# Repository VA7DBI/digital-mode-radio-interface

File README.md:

A basic project to provide an isolated audio and CAT control interface.   Connectes to the host PC via USB and provides a Serial Port providing a CAT Control interface and an Audio CODEC.

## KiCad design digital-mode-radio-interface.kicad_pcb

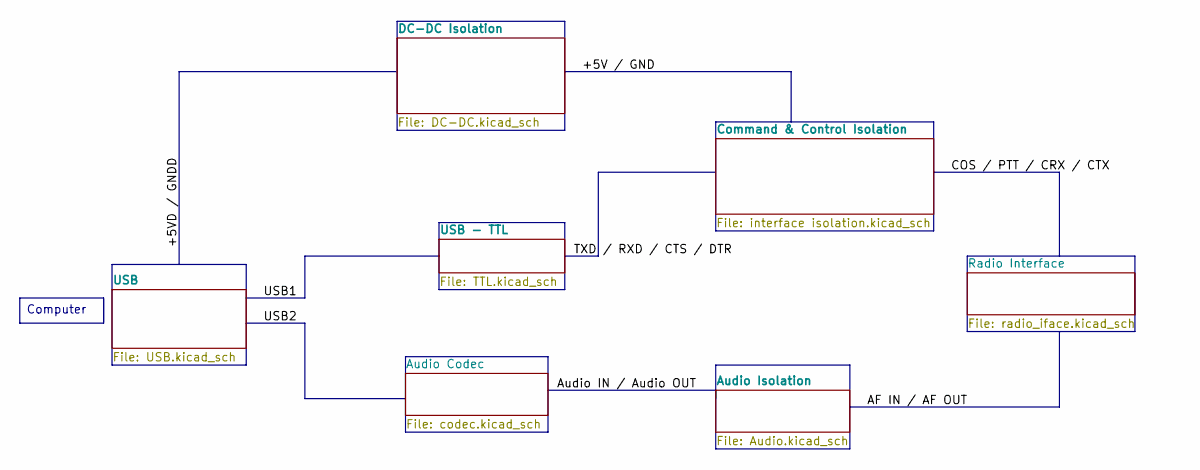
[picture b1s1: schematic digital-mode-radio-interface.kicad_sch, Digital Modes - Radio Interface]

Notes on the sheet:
Computer

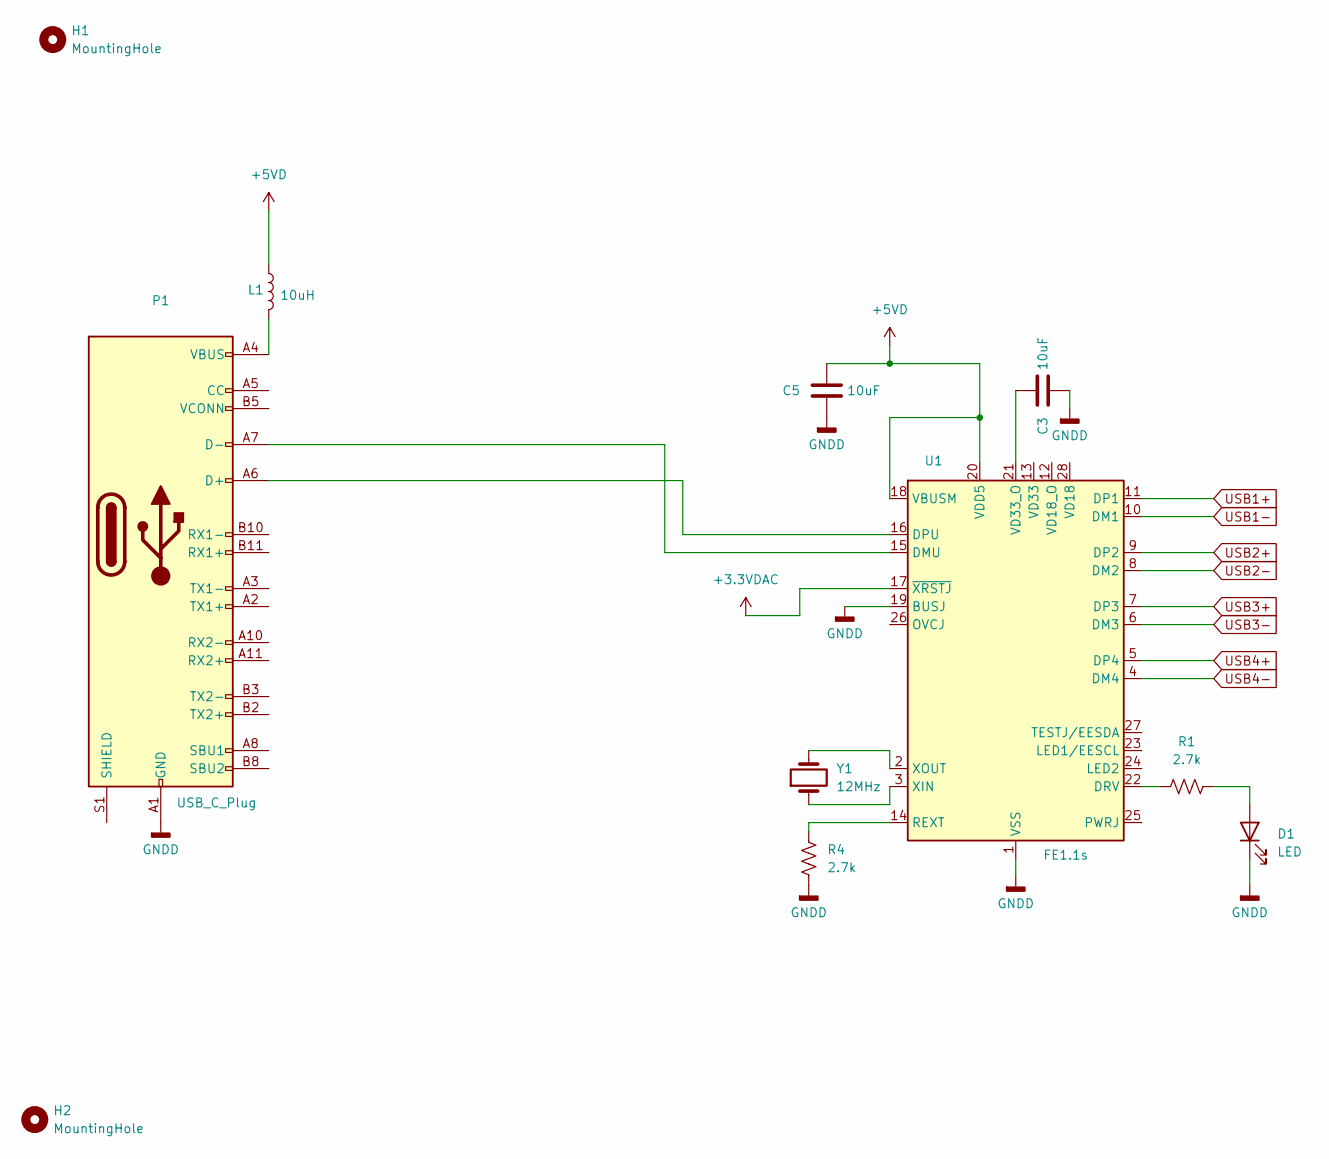
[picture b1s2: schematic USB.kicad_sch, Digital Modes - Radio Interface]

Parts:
C3, C5: 10uF; C_0201_0603Metric
D1: LED; LED_0201_0603Metric
H1, H2: MountingHole; MountingHole_3.2mm_M3
L1: 10uH; L_CommonModeChoke_Coilcraft_0805USB
P1: USB_C_Plug; USB_C_Receptacle_GCT_USB4085
R1, R4: 2.7k; R_0201_0603Metric
U1: FE1.1s; SSOP-28_3.9x9.9mm_P0.635mm
Y1: 12MHz; Crystal_SMD_FOX_FE-2Pin_7.5x5.0mm_HandSoldering

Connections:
+3.3VDAC: U1.17 (~XRSTJ); also elsewhere on the board
+5VD: C5.1, L1.1, U1.18 (VBUSM), U1.20 (VDD5); also elsewhere on the board
GNDD: C3.2, C5.2, D1.1 (K), P1.A1 (GND), P1.A12 (GND), P1.B1 (GND), P1.B12 (GND), R4.2, U1.1 (VSS), U1.19 (BUSJ); also elsewhere on the board
unnamed: D1.2 (A), R1.2
unnamed: L1.2, P1.A4 (VBUS), P1.A9 (VBUS), P1.B4 (VBUS), P1.B9 (VBUS)
unnamed: P1.A6 (D+), U1.16 (DPU)
unnamed: P1.A7 (D-), U1.15 (DMU)
unnamed: R1.1, U1.22 (DRV)
unnamed: R4.1, U1.14 (REXT)
unnamed: C3.1, U1.21 (VD33_O)
unnamed: U1.3 (XIN), Y1.1
unnamed: U1.2 (XOUT), Y1.2
USB1+: U1.11 (DP1); also elsewhere on the board
USB1-: U1.10 (DM1); also elsewhere on the board
USB2+: U1.9 (DP2)
USB2-: U1.8 (DM2)
USB3+: U1.7 (DP3)
USB3-: U1.6 (DM3)
USB4+: U1.5 (DP4)
USB4-: U1.4 (DM4)

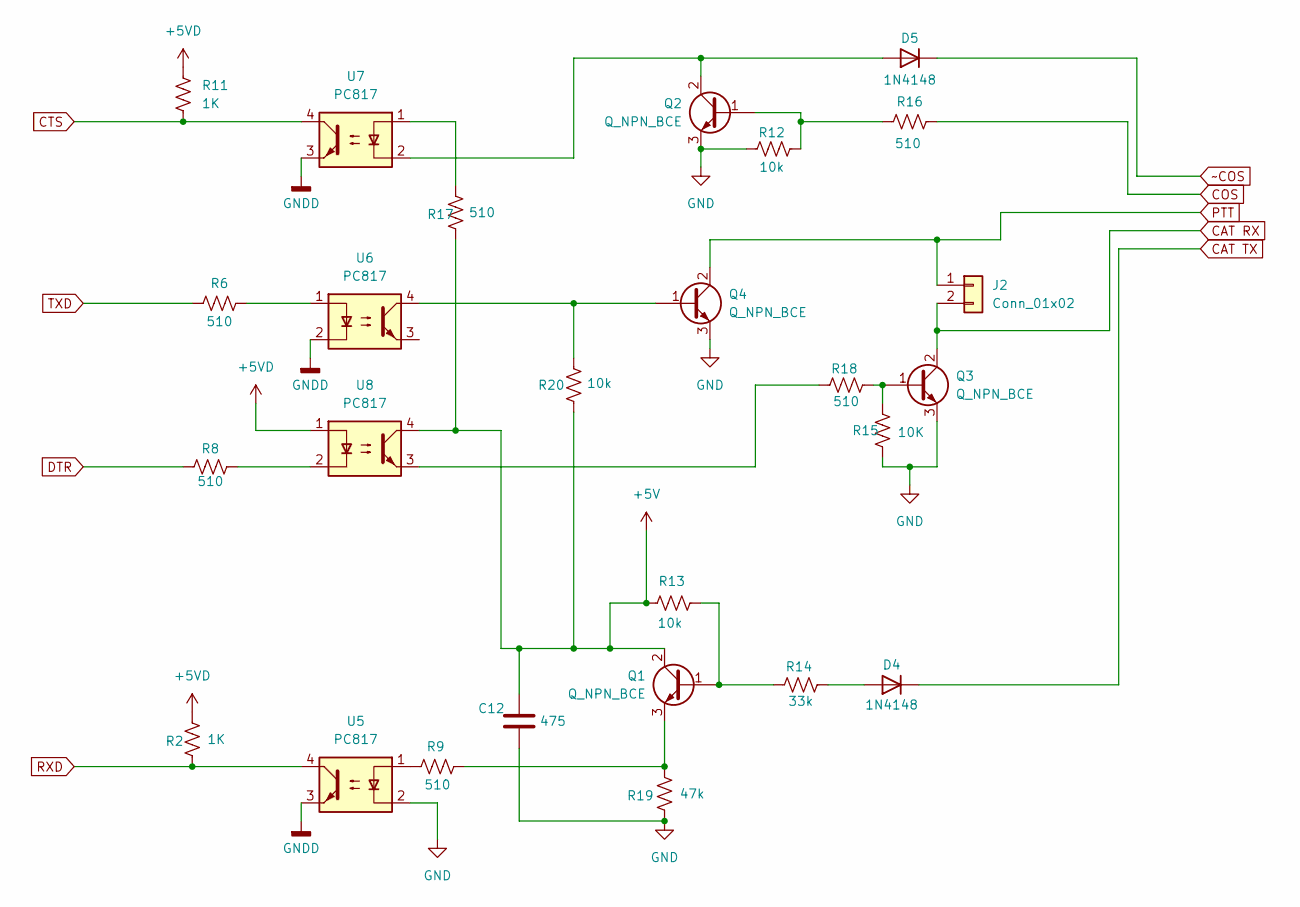
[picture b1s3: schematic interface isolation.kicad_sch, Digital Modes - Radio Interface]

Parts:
C12: 475; C_0201_0603Metric
D4, D5: 1N4148; D_0603_1608Metric
J2: Conn_01x02; PinHeader_1x02_P1.00mm_Vertical
Q1, Q2, Q3, Q4: Q_NPN_BCE; SOT-23-3
R2, R11: 1K; R_0201_0603Metric
R6, R8, R9, R16, R17, R18: 510; R_0201_0603Metric
R12, R13, R20: 10k; R_0201_0603Metric
R14: 33k; R_0201_0603Metric
R15: 10K; R_0201_0603Metric
R19: 47k; R_0201_0603Metric
U5, U6, U7, U8: PC817; DIP-4_W7.62mm

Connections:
+5V: C12.1, Q1.2 (C), R13.1, R17.1, R20.1, U8.4; also elsewhere on the board
+5VD: R2.1, R11.1, U8.1; also elsewhere on the board
CTS: R11.2, U7.4; also elsewhere on the board
DTR: R8.1; also elsewhere on the board
GND: C12.2, Q2.3 (E), Q3.3 (E), Q4.3 (E), R12.1, R15.1, R19.1, U5.2; also elsewhere on the board
GNDD: U5.3, U6.2, U7.3; also elsewhere on the board
unnamed: D4.2 (A), R14.2
unnamed 22: D4.1 (K); also elsewhere on the board
unnamed: D5.2 (A), Q2.2 (C), U7.2
unnamed 24: D5.1 (K); also elsewhere on the board
unnamed 28: J2.1, Q4.2 (C); also elsewhere on the board
unnamed 29: J2.2, Q3.2 (C); also elsewhere on the board
unnamed 30: R16.2; also elsewhere on the board
unnamed: Q1.1 (B), R13.2, R14.1
unnamed: Q1.3 (E), R9.2, R19.2
unnamed: Q2.1 (B), R12.2, R16.1
unnamed: Q3.1 (B), R15.2, R18.2
unnamed: Q4.1 (B), R20.2, U6.4
unnamed: R6.2, U6.1
unnamed: R8.2, U8.2
unnamed: R9.1, U5.1
unnamed: R17.2, U7.1
unnamed: R18.1, U8.3
RXD: R2.2, U5.4; also elsewhere on the board
TXD: R6.1; also elsewhere on the board

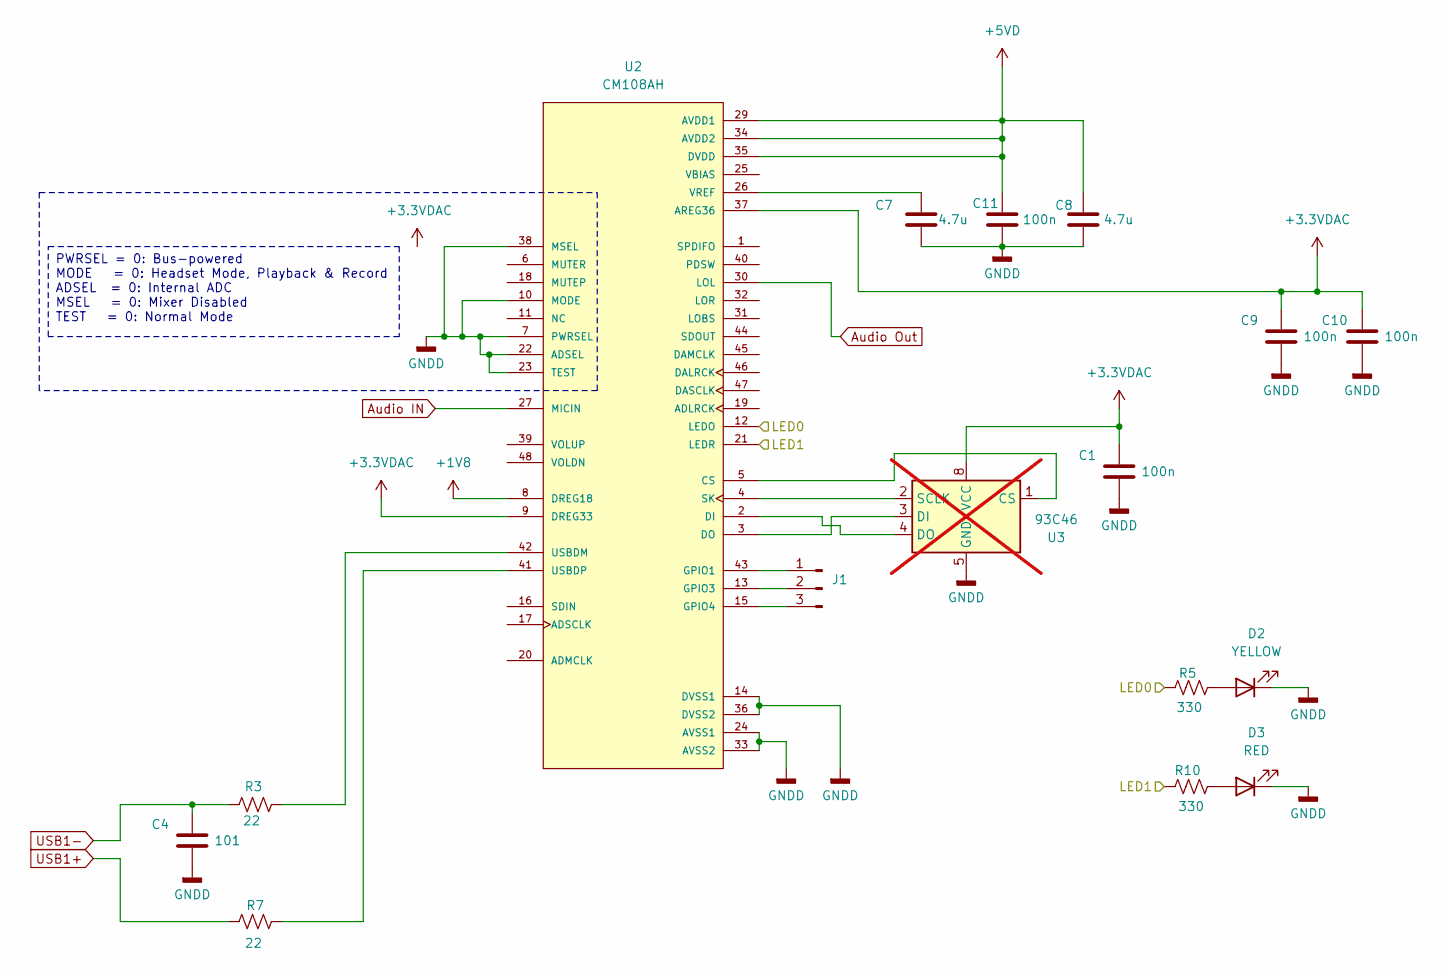
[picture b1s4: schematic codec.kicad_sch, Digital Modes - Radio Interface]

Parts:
C1, C9, C10, C11: 100n; C_0201_0603Metric
C4: 101; C_0201_0603Metric
C7, C8: 4.7u; C_0201_0603Metric
D2: YELLOW; LED_0201_0603Metric
D3: RED; LED_0201_0603Metric
J1: Conn_01x03_Pin; PinHeader_1x03_P1.00mm_Vertical
R3, R7: 22; R_0201_0603Metric
R5, R10: 330; R_0201_0603Metric
U2: CM108AH; LQFP-48_7x7mm_P0.5mm; PARTREV 1.9
U3: 93C46; SOIC-8_3.9x4.9mm_P1.27mm; not fitted

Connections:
+1V8: U2.8 (DREG18)
+3.3VDAC: C1.1, C9.1, C10.1, U2.9 (DREG33), U2.37 (AREG36), U3.8 (VCC); also elsewhere on the board
+5VD: C8.1, C11.1, U2.29 (AVDD1), U2.34 (AVDD2), U2.35 (DVDD); also elsewhere on the board
/Audio Codec/LED0: R5.1, U2.12 (LEDO)
/Audio Codec/LED1: R10.1, U2.21 (LEDR)
Audio IN: U2.27 (MICIN); also elsewhere on the board
Audio Out: U2.30 (LOL); also elsewhere on the board
GNDD: C1.2, C4.2, C7.2, C8.2, C9.2, C10.2, C11.2, D2.1 (K), D3.1 (K), U2.7 (PWRSEL), U2.10 (MODE), U2.14 (DVSS1), U2.22 (ADSEL), U2.23 (TEST), U2.24 (AVSS1), U2.33 (AVSS2), U2.36 (DVSS2), U2.38 (MSEL), U3.5 (GND); also elsewhere on the board
unnamed: D2.2 (A), R5.2
unnamed: D3.2 (A), R10.2
unnamed: J1.1, U2.43 (GPIO1)
unnamed: J1.2, U2.13 (GPIO3)
unnamed: J1.3, U2.15 (GPIO4)
unnamed: U2.5 (CS), U3.1 (CS)
unnamed: U2.2 (DI), U3.4 (DO)
unnamed: U2.3 (DO), U3.3 (DI)
unnamed: U2.4 (SK), U3.2 (SCLK)
unnamed: R3.2, U2.42 (USBDM)
unnamed: R7.2, U2.41 (USBDP)
unnamed: C7.1, U2.26 (VREF)
USB1+: R7.1; also elsewhere on the board
USB1-: C4.1, R3.1; also elsewhere on the board

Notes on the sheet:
PWRSEL = 0: Bus-powered MODE = 0: Headset Mode, Playback & Record ADSEL = 0: Internal ADC MSEL = 0: Mixer Disabled TEST = 0: Normal Mode

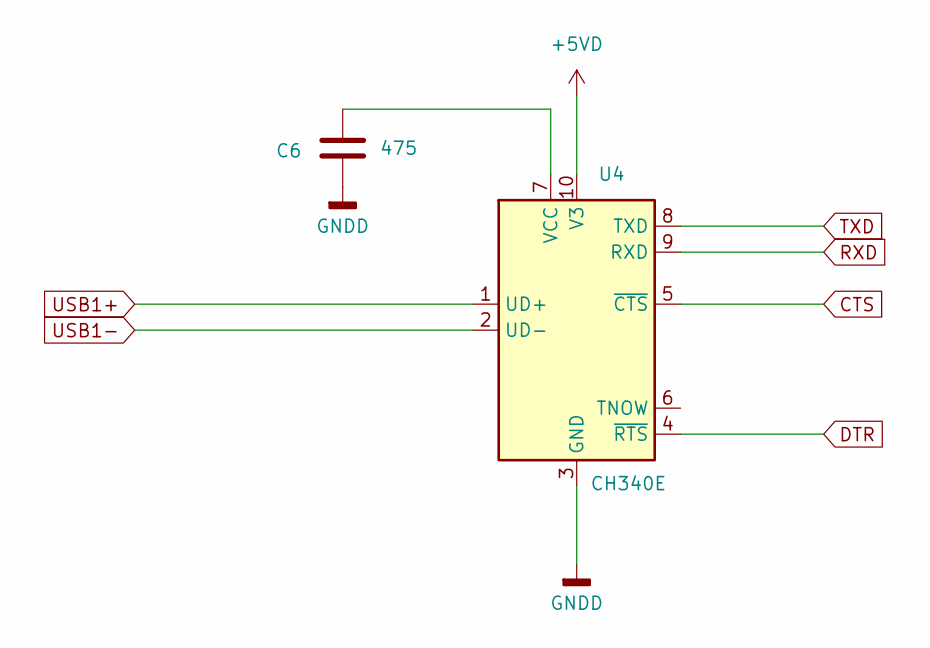
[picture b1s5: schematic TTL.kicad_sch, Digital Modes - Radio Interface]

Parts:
C6: 475; C_0201_0603Metric
U4: CH340E; MSOP-10_3x3mm_P0.5mm

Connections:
+5VD: U4.10 (V3); also elsewhere on the board
CTS: U4.5 (~CTS); also elsewhere on the board
DTR: U4.4 (~RTS); also elsewhere on the board
GNDD: C6.2, U4.3 (GND); also elsewhere on the board
unnamed: C6.1, U4.7 (VCC)
RXD: U4.9 (RXD); also elsewhere on the board
TXD: U4.8 (TXD); also elsewhere on the board
USB1+: U4.1 (UD+); also elsewhere on the board
USB1-: U4.2 (UD-); also elsewhere on the board

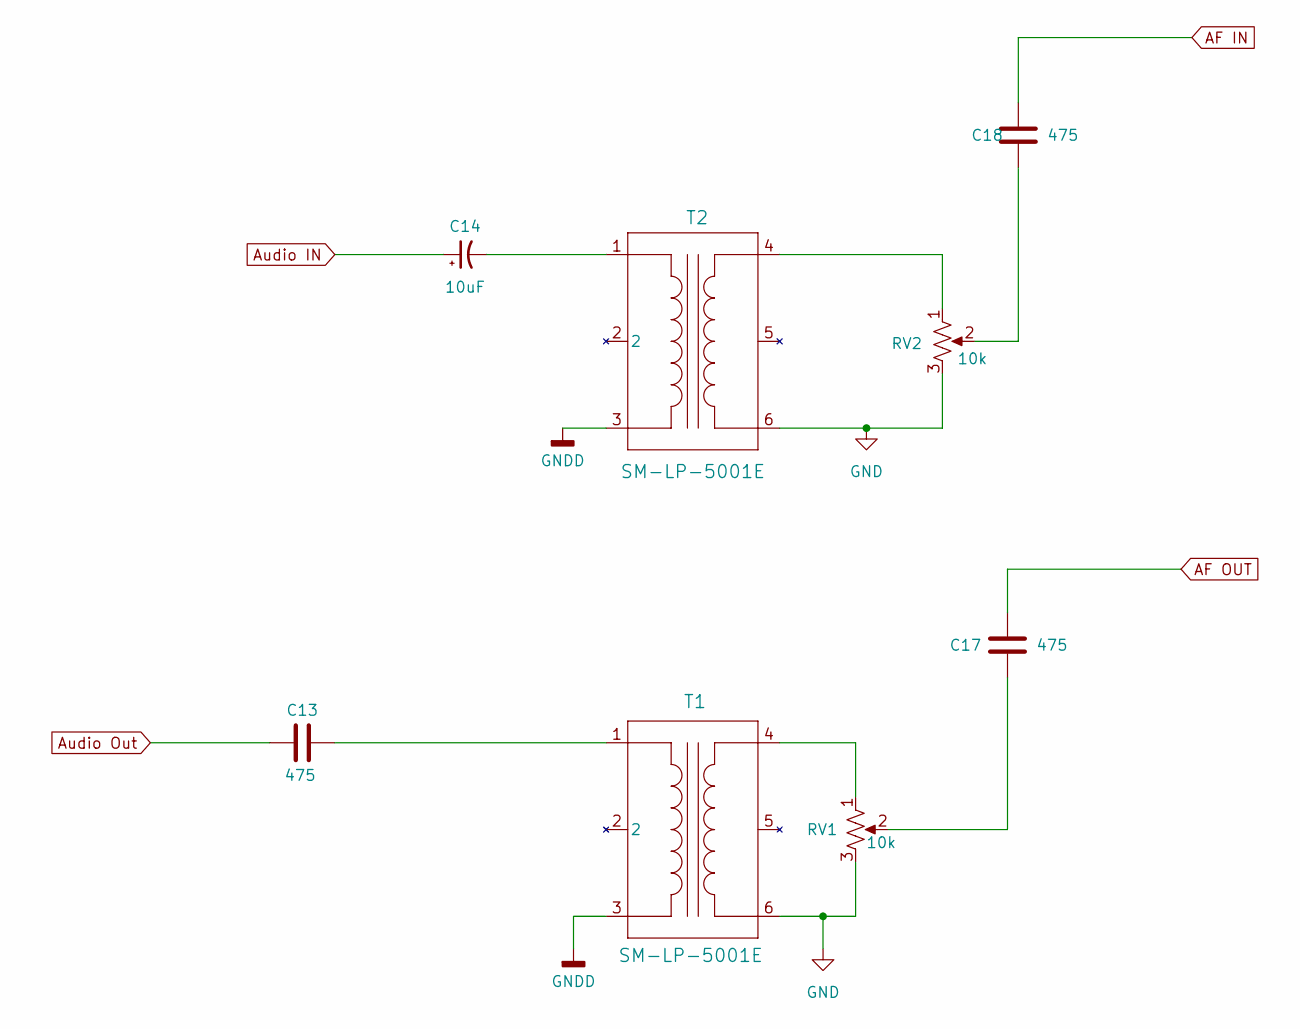
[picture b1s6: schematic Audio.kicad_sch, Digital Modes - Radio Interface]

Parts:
C13, C17, C18: 475; C_0201_0603Metric
C14: 10uF; C_0201_0603Metric
RV1, RV2: 10k; Potentiometer_ACP_CA6-VSMD_Vertical
T1, T2: SM-LP-5001E; RES6_SM-LP-5001E_BRN-L

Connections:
AF IN: C18.1; also elsewhere on the board
AF OUT: C17.1; also elsewhere on the board
Audio IN: C14.1; also elsewhere on the board
Audio Out: C13.1; also elsewhere on the board
GND: RV1.3, RV2.3, T1.6, T2.6; also elsewhere on the board
GNDD: T1.3, T2.3; also elsewhere on the board
unnamed: C13.2, T1.1
unnamed: C14.2, T2.1
unnamed: C17.2, RV1.2
unnamed: C18.2, RV2.2
unnamed: RV1.1, T1.4
unnamed: RV2.1, T2.4

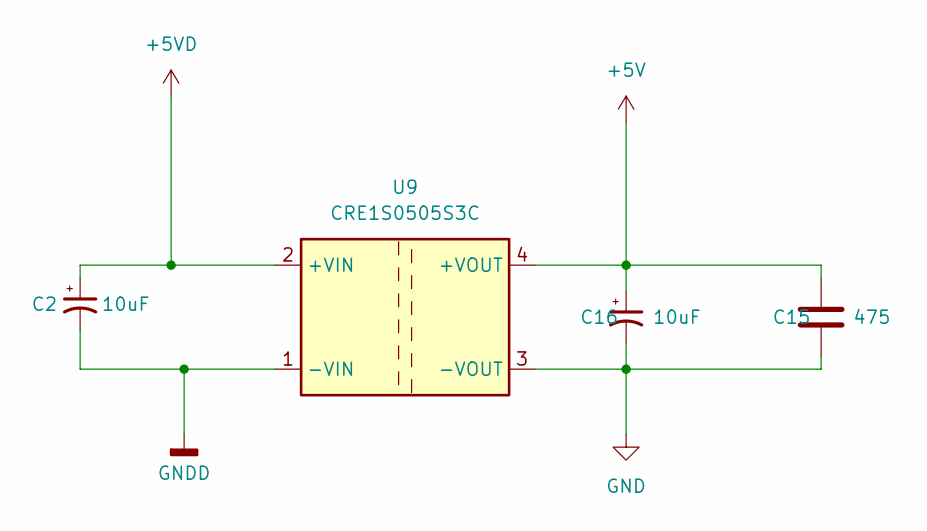
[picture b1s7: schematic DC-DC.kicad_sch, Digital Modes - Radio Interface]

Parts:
C2, C16: 10uF; C_0201_0603Metric
C15: 475; C_0201_0603Metric
U9: CRE1S0505S3C; Converter_DCDC_Murata_CRE1xxxxxx3C_THT

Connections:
+5V: C15.1, C16.1, U9.4 (+VOUT); also elsewhere on the board
+5VD: C2.1, U9.2 (+VIN); also elsewhere on the board
GND: C15.2, C16.2, U9.3 (-VOUT); also elsewhere on the board
GNDD: C2.2, U9.1 (-VIN); also elsewhere on the board

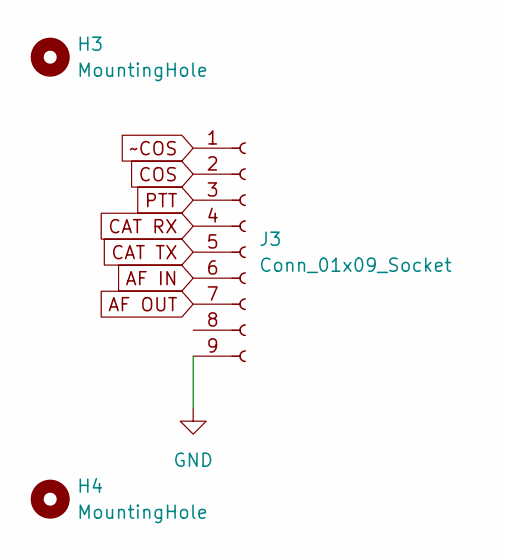
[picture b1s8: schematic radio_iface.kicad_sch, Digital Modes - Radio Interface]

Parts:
H3, H4: MountingHole; MountingHole_3.2mm_M3
J3: Conn_01x09_Socket; DSUB-9_Female_Horizontal_P2.77x2.84mm_EdgePinOffset4.94mm_H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

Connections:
AF IN: J3.6; also elsewhere on the board
AF OUT: J3.7; also elsewhere on the board
GND: J3.9; also elsewhere on the board
unnamed 22: J3.5; also elsewhere on the board
unnamed 24: J3.1; also elsewhere on the board
unnamed 28: J3.3; also elsewhere on the board
unnamed 29: J3.4; also elsewhere on the board
unnamed 30: J3.2; also elsewhere on the board

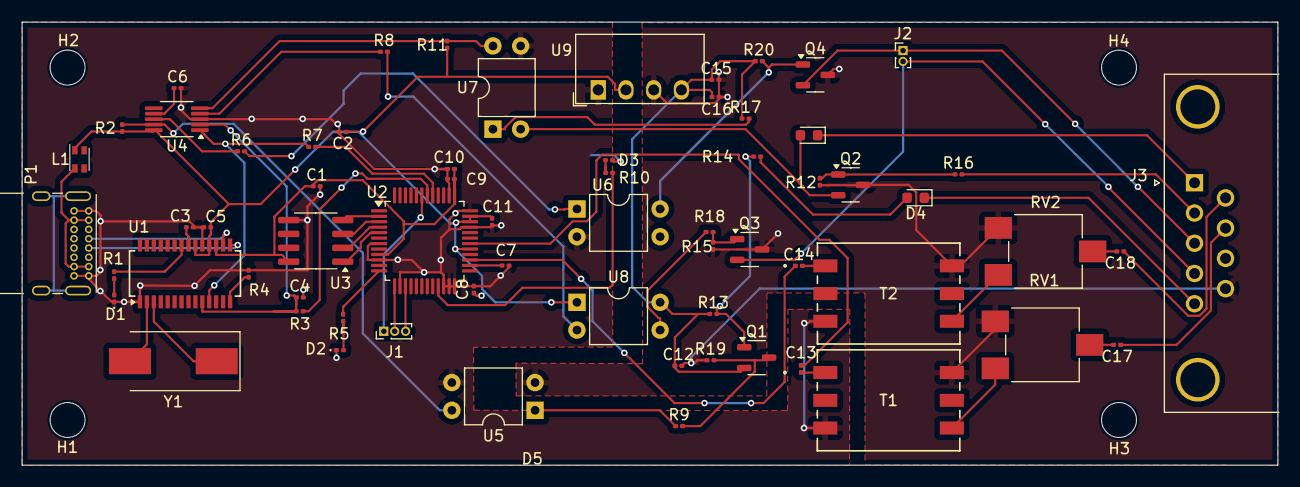
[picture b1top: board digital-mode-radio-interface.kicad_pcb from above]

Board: 2 copper layers, 115.0 x 40.6 mm, 70 parts (0 on the bottom side), 62 nets.

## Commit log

2024-05-30 Checkin for safe keeping.
    This is a work in progress, a number of blocks are still not finished, no foot prints assigned etc.
2024-05-30 Add ~_auto* to git ignore
2024-06-02 Add CM108B codex schematic parts and plumb to USB, and Audio Isolation
2024-06-03 Assign footprints to devices
2024-06-03 Update to exclude backup and lock files
2024-06-03 WIP checkin of PCB layout
2024-06-03 Add Bourne 600Ohm 1:1 audio transformer footprints
2024-06-03 Place Audio tranformers and cleanup routing. Re-annotate based on geographical layout.
2024-06-03 Move Radio interface onto it's own sheet, Add mounting holes and case outline
2025-02-20 Update jlpcb.yml to use actions v4
2025-02-20 Update 3d-images.yml to use latest actions
2025-02-20 Update jlpcb.yml to use kicad8 vs 5 typo
2025-02-20 Refresh with kicad 8.0.8
2025-02-20 Update jlpcb.yml to follow latest best practices
2025-02-20 Update jlpcb.yml actions/upload-artifact to V4
2025-03-01 kiCAD 9.0
